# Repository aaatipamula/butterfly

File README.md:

# The Butterfly Keyboard

## Origin

I started this project for a few reasons:

1. I've wanted to try designing my own pcb
2. I like the layout of the [corne](https://github.com/foostan/crkbd) keyboard 
3. I wanted a lightweight and relatively small keyboard to bring around with me

## Design

As mentioned before I took a lot of inspiration from the very popular  [corne](https://github.com/foostan/crkbd) designed by foostan.  Most of the layout was taken directly from the corne, however, a few key changes were made to fit my constraints. They are as follows: 

1. The board is a singular piece which allows for the use of one microcontroller
2. Each "half" of the board is angled in at 13 degrees for a more comfortable typing position
3. The switch footprints are a solder-only mx/choc hybrid (taken from foostan's [keyboard](https://github.com/foostan/kbd) library)

The intended use I had for this board was to simply use the pcb as the entire board. I wanted to keep the board as thin and small as possible. A foam pad should cover the bottom of the board to protect it from damage. <br> <br>
The name came about as I was outlining the pcb for the board. The shape heavily reminded me of a butterfly and I decided to name the board as such!

## Pictures

### PCB Design

### 3D Render of the Front

### 3D Render of the Back

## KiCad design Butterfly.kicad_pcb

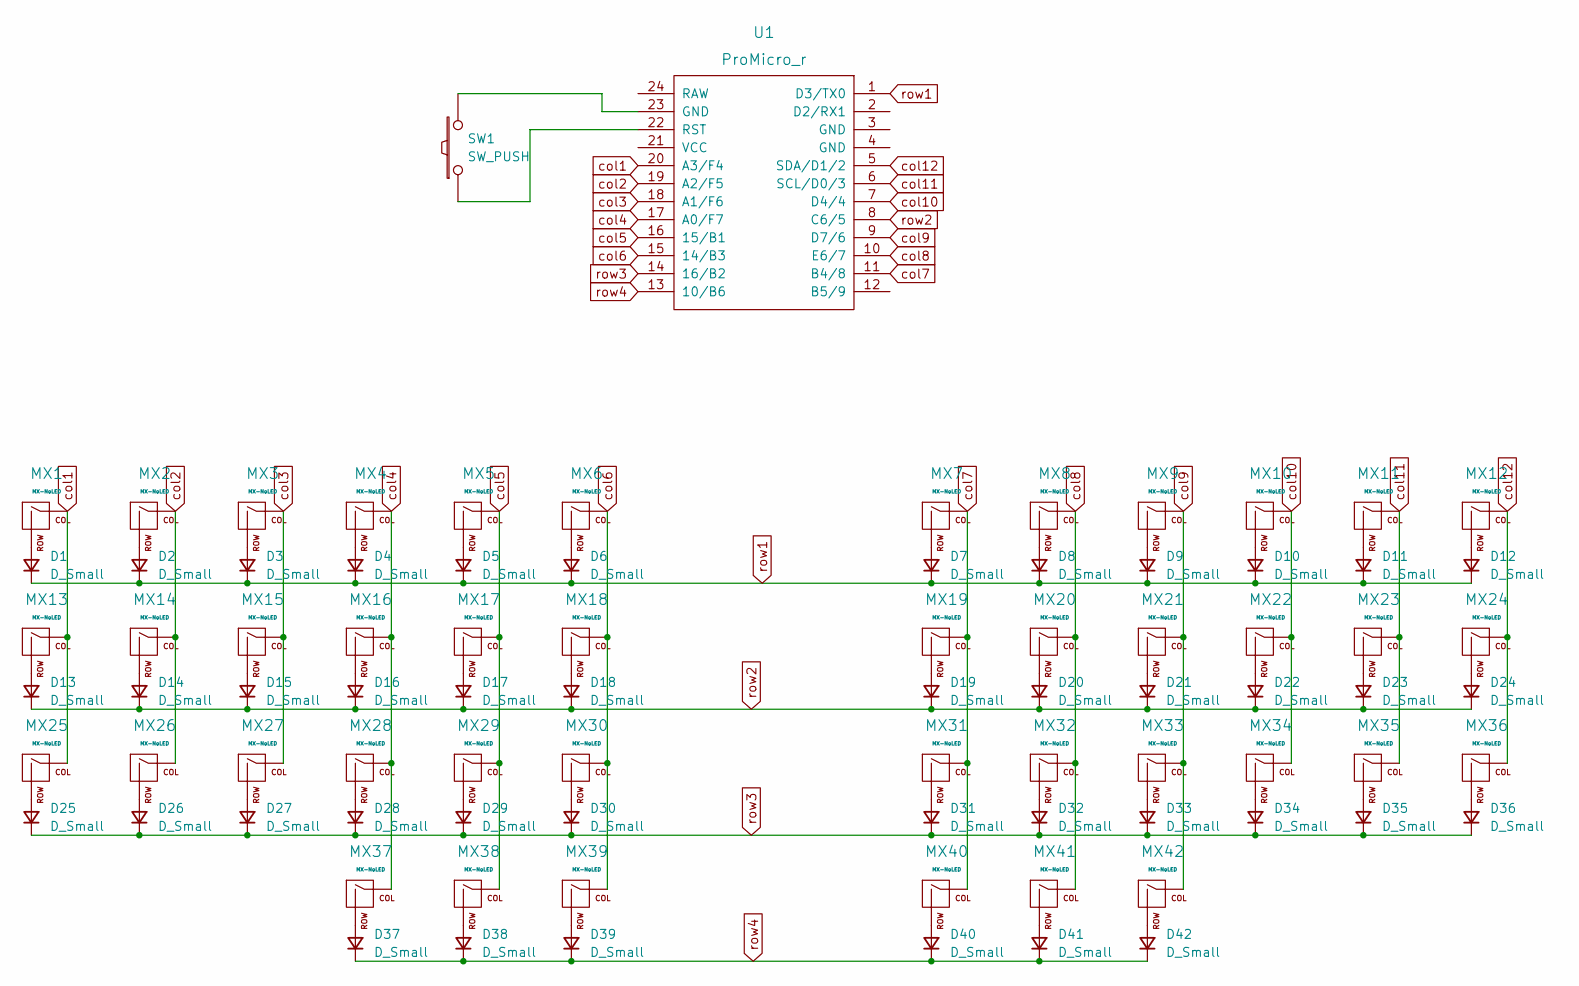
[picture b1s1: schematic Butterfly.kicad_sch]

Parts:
D1, D2, D3, D4, D5, D6, D7, D8, D9, D10, D11, D12, D13, D14, D15, D16, D17, D18, D19, D20, D21, D22, D23, D24, D25, D26, D27, D28, D29, D30, D31, D32, D33, D34, D35, D36, D37, D38, D39, D40, D41, D42: D_Small; D_SOD-123
MX1, MX2, MX3, MX4, MX5, MX6, MX7, MX8, MX9, MX10, MX11, MX12, MX13, MX14, MX15, MX16, MX17, MX18, MX19, MX20, MX21, MX22, MX23, MX24, MX25, MX26, MX27, MX28, MX29, MX30, MX31, MX32, MX33, MX34, MX35, MX36, MX37, MX38, MX41, MX42: MX-NoLED; CherryMX_Choc_1u
MX39, MX40: MX-NoLED; CherryMX_Choc_1.5u
SW1: SW_PUSH; ResetSW
U1: ProMicro_r; ProMicro_v3

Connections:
unnamed: D1.2 (A), MX1.2 (ROW)
unnamed: D2.2 (A), MX2.2 (ROW)
unnamed: D3.2 (A), MX3.2 (ROW)
unnamed: D4.2 (A), MX4.2 (ROW)
unnamed: D5.2 (A), MX5.2 (ROW)
unnamed: D6.2 (A), MX6.2 (ROW)
unnamed: D7.2 (A), MX7.2 (ROW)
unnamed: D8.2 (A), MX8.2 (ROW)
unnamed: D9.2 (A), MX9.2 (ROW)
unnamed: D10.2 (A), MX10.2 (ROW)
unnamed: D11.2 (A), MX11.2 (ROW)
unnamed: D12.2 (A), MX12.2 (ROW)
unnamed: D13.2 (A), MX13.2 (ROW)
unnamed: D14.2 (A), MX14.2 (ROW)
unnamed: D15.2 (A), MX15.2 (ROW)
unnamed: D16.2 (A), MX16.2 (ROW)
unnamed: D17.2 (A), MX17.2 (ROW)
unnamed: D18.2 (A), MX18.2 (ROW)
unnamed: D19.2 (A), MX19.2 (ROW)
unnamed: D20.2 (A), MX20.2 (ROW)
unnamed: D21.2 (A), MX21.2 (ROW)
unnamed: D22.2 (A), MX22.2 (ROW)
unnamed: D23.2 (A), MX23.2 (ROW)
unnamed: D24.2 (A), MX24.2 (ROW)
unnamed: D25.2 (A), MX25.2 (ROW)
unnamed: D26.2 (A), MX26.2 (ROW)
unnamed: D27.2 (A), MX27.2 (ROW)
unnamed: D28.2 (A), MX28.2 (ROW)
unnamed: D29.2 (A), MX29.2 (ROW)
unnamed: D30.2 (A), MX30.2 (ROW)
unnamed: D31.2 (A), MX31.2 (ROW)
unnamed: D32.2 (A), MX32.2 (ROW)
unnamed: D33.2 (A), MX33.2 (ROW)
unnamed: D34.2 (A), MX34.2 (ROW)
unnamed: D35.2 (A), MX35.2 (ROW)
unnamed: D36.2 (A), MX36.2 (ROW)
unnamed: D37.2 (A), MX37.2 (ROW)
unnamed: D38.2 (A), MX38.2 (ROW)
unnamed: D39.2 (A), MX39.2 (ROW)
unnamed: D40.2 (A), MX40.2 (ROW)
unnamed: D41.2 (A), MX41.2 (ROW)
unnamed: D42.2 (A), MX42.2 (ROW)
unnamed: SW1.1, U1.22 (RST)
unnamed: SW1.2, U1.23 (GND)
col1: MX1.1 (COL), MX13.1 (COL), MX25.1 (COL), U1.20 (A3/F4)
col2: MX2.1 (COL), MX14.1 (COL), MX26.1 (COL), U1.19 (A2/F5)
col3: MX3.1 (COL), MX15.1 (COL), MX27.1 (COL), U1.18 (A1/F6)
col4: MX4.1 (COL), MX16.1 (COL), MX28.1 (COL), MX37.1 (COL), U1.17 (A0/F7)
col5: MX5.1 (COL), MX17.1 (COL), MX29.1 (COL), MX38.1 (COL), U1.16 (15/B1)
col6: MX6.1 (COL), MX18.1 (COL), MX30.1 (COL), MX39.1 (COL), U1.15 (14/B3)
col7: MX7.1 (COL), MX19.1 (COL), MX31.1 (COL), MX40.1 (COL), U1.11 (B4/8)
col8: MX8.1 (COL), MX20.1 (COL), MX32.1 (COL), MX41.1 (COL), U1.10 (E6/7)
col9: MX9.1 (COL), MX21.1 (COL), MX33.1 (COL), MX42.1 (COL), U1.9 (D7/6)
col10: MX10.1 (COL), MX22.1 (COL), MX34.1 (COL), U1.7 (D4/4)
col11: MX11.1 (COL), MX23.1 (COL), MX35.1 (COL), U1.6 (SCL/D0/3)
col12: MX12.1 (COL), MX24.1 (COL), MX36.1 (COL), U1.5 (SDA/D1/2)
row1: D1.1 (K), D2.1 (K), D3.1 (K), D4.1 (K), D5.1 (K), D6.1 (K), D7.1 (K), D8.1 (K), D9.1 (K), D10.1 (K), D11.1 (K), D12.1 (K), U1.1 (D3/TX0)
row2: D13.1 (K), D14.1 (K), D15.1 (K), D16.1 (K), D17.1 (K), D18.1 (K), D19.1 (K), D20.1 (K), D21.1 (K), D22.1 (K), D23.1 (K), D24.1 (K), U1.8 (C6/5)
row3: D25.1 (K), D26.1 (K), D27.1 (K), D28.1 (K), D29.1 (K), D30.1 (K), D31.1 (K), D32.1 (K), D33.1 (K), D34.1 (K), D35.1 (K), D36.1 (K), U1.14 (16/B2)
row4: D37.1 (K), D38.1 (K), D39.1 (K), D40.1 (K), D41.1 (K), D42.1 (K), U1.13 (10/B6)

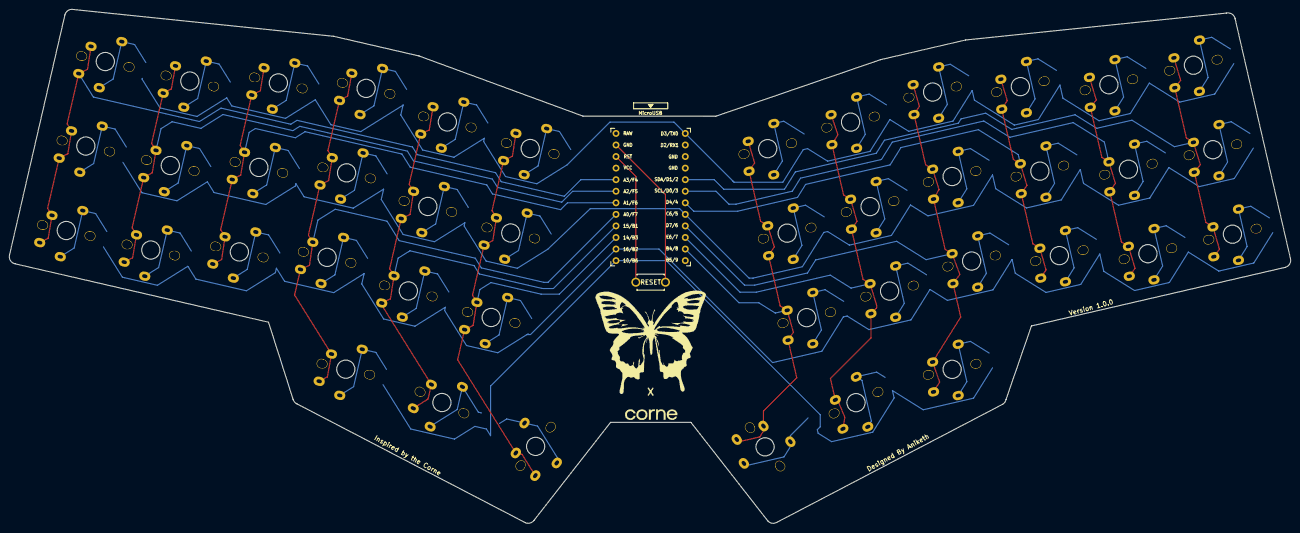
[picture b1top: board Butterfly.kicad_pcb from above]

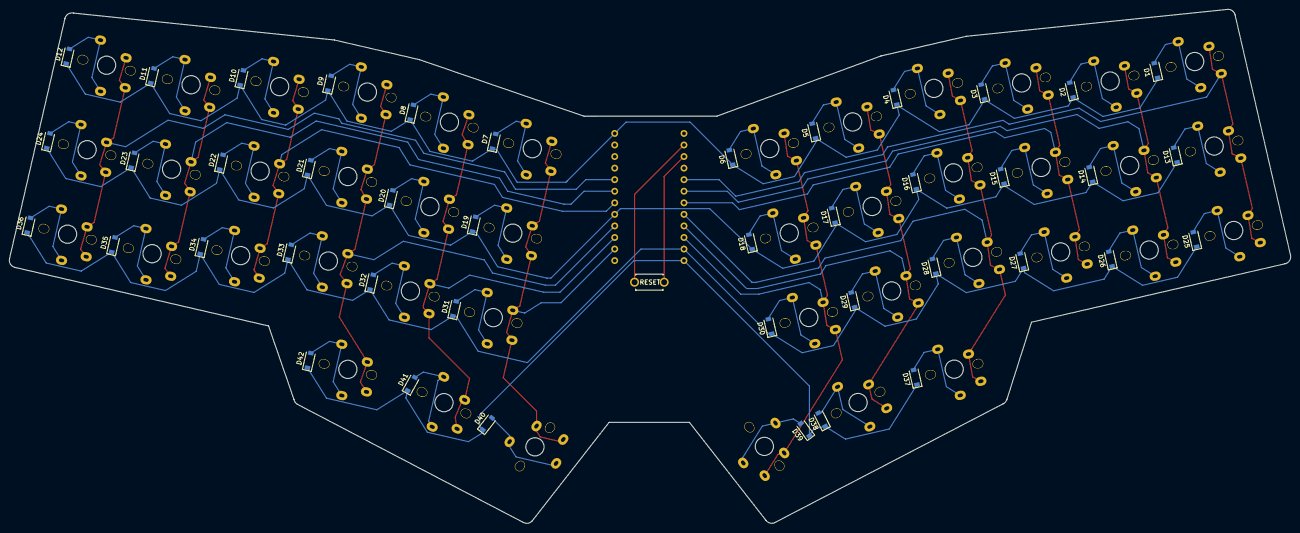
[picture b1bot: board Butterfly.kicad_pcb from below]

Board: 2 copper layers, 281.5 x 112.9 mm, 87 parts (42 on the bottom side), 60 nets.

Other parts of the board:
Butterfly: X; butterfly_small

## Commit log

2023-05-09 inital commit
